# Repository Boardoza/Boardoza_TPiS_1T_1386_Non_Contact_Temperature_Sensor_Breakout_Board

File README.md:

# Boardoza TPiS 1T 1386 L5.5 H Thermopile Sensor Breakout Board

The **Boardoza TPiS 1T 1386 L5.5 H Breakout Board** is a non-contact infrared temperature sensor board designed for makers, developers, and embedded system enthusiasts who need accurate temperature measurements without physical contact. It uses the **Excelitas TPiS 1T 1386 L5.5 H** thermopile sensor to measure object temperature in a fast, hygienic, and contactless way, making it ideal for projects where traditional contact sensors are not suitable.

The onboard sensor provides strong thermal stabilization, ensuring reliable and consistent measurements even under harsh or changing environmental conditions. Communication is handled via the **I²C interface**, allowing easy integration with popular development platforms such as Arduino, ESP32, and Raspberry Pi. This breakout board is well suited for **maker projects and prototypes including non-contact thermometers, industrial temperature monitoring, HVAC systems, smart home applications, medical devices, and general IoT-based temperature sensing solutions**.

## [Click here to purchase!](https://www.ozdisan.com/p/gelistirme-kitleri-ve-aksesuarlari-617/boardoza-tpis-1t-1386-1202719)
| Front Side | Back Side |
|:---:|:---:|
|  |  |

---

## Key Features

- **Non-Contact Temperature Measurement:** Measures object temperature without physical contact using infrared sensing technology.
- **Excelitas Thermopile Sensor:** Equipped with the **TPiS 1T 1386 L5.5 H** medical-grade thermopile sensor.
- **Thermal Stabilization:** Delivers stable and reliable temperature readings even in harsh or changing environmental conditions.
- **I²C Communication Interface:** Standard I²C protocol for easy integration with microcontrollers and development boards.
- **Wide Supply Voltage Support:** Compatible with both **3.3V and 5V** systems.
- **Interrupt Output:** Open-drain, active-low interrupt pin for event-based temperature monitoring.

---

## Technical Specifications

**Model:** TPiS 1T 1386 L5.5 H  
**Manufacturer:** Boardoza  
**Manufacturer IC:** Excelitas Technologies  
**Supply Voltage:** 3.3V - 5V  
**Functions:** Non-contact infrared temperature sensor  
**Communication Interface:** I²C  
**I²C Clock Speed:** Up to 400 kHz (clock stretching supported)  
**Interrupt Output:** Open-drain, active-low  
**Maximum Current per Pin:** −100 mA to +100 mA  
**Storage Temperature:** −40 °C to +105 °C  
**Operating Temperature:** −20 °C to +105 °C  
**Board Dimensions:** 20 mm × 40 mm

---

## Board Pinout

### ( J1 ) I²C & Power Connector

| Pin Number | Pin Name | Description |
|:---:|:---:|---|
| 1 | VCC | Power supply input (3.3V - 5V) |
| 2 | SCL | I²C serial clock line |
| 3 | SDA | I²C bidirectional data line |
| 4 | GND | Ground |

### ( J2 ) Interrupt Connector

| Pin Number | Pin Name | Description |
|:---:|:---:|---|
| 1 | INT | Open-drain, active-low interrupt output. Cleared by reading sensor registers |

---

## Board Dimensions

---

## Step Files

[Boardoza TPiS_1T_1386L5.step](./assets/TPiS_1T_1386L5%20Step.step)

---

## Datasheet

[TPiS 1T 1386 L5.5 H Datasheet.pdf](./assets/TPiS_1T_1386L5%20Datasheet.pdf)

---

## Version History

- V1.0.0 – Initial Release

---

## Support

- If you have any questions or need support, please contact **support@boardoza.com**

---

## **License**

This repository contains both hardware and software components:

### **Hardware Design**

[![CC BY-SA 4.0][cc-by-sa-shield]][cc-by-sa]

All hardware design files are licensed under [Creative Commons Attribution-ShareAlike 4.0 International License][cc-by-sa].

[cc-by-sa]: http://creativecommons.org/licenses/by-sa/4.0/
[cc-by-sa-shield]: https://img.shields.io/badge/License-CC%20BY--SA%204.0-lightgrey.svg

### **Software/Firmware**

[![BSD-3-Clause][bsd-shield]][bsd]

All software and firmware are licensed under [BSD 3-Clause License][bsd].

[bsd]: https://opensource.org/licenses/BSD-3-Clause
[bsd-shield]: https://img.shields.io/badge/License-BSD%203--Clause-blue.svg

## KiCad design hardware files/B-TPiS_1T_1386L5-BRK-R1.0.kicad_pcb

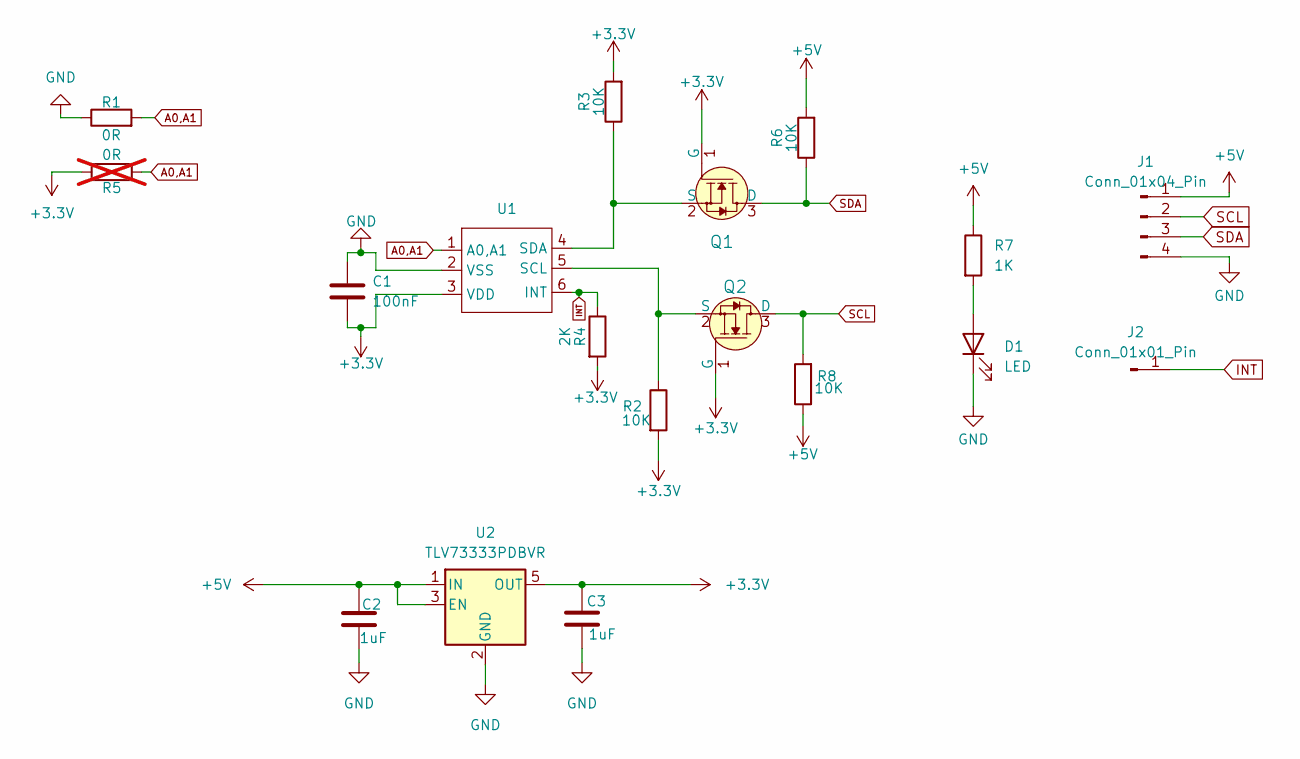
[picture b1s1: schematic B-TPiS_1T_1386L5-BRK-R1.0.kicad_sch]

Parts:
C1: 100nF; C_0603_1608Metric; MPN CL10B104KB8NNNC
C2, C3: 1uF; C_0603_1608Metric; MPN CL10A105KO8NNNC
D1: LED; LED_0603_1608Metric; MPN LTST-C190KRKT
J1: Conn_01x04_Pin; 2317-04S_1x04_P2.50mm_Vertical
J2: Conn_01x01_Pin; PinHeader_1x01_P2.54mm_Vertical
Q1, Q2: 2N7002-7-F; SOT-23-3; MPN 2N7002_R1_00001; Digi-Key_PN 2N7002-FDICT-ND
R1: 0R; R_0603_1608Metric; MPN CRT03J7-R0R0
R2, R3, R6, R8: 10K; R_0603_1608Metric; MPN 0603WGJ0103T5E
R4: 2K; R_0603_1608Metric; MPN 0603SAJ0202T5E
R5: 0R; R_0603_1608Metric; MPN CRT03J7-R0R0; not fitted
R7: 1K; R_0603_1608Metric; MPN CRT03J7E1001
U1: TPiS 1T 1386
U2: TLV73333PDBVR; SOT-23-5

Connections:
+3.3V: C1.2, C3.1, Q1.1 (G), Q2.1 (G), R2.2, R3.2, R4.2, R5.2, U1.3 (VDD), U2.5 (OUT)
+5V: C2.1, J1.1, R6.2, R7.1, R8.1, U2.1 (IN), U2.3 (EN)
A0,A1: R1.2, R5.1, U1.1 (A0,A1)
GND: C1.1, C2.2, C3.2, D1.1 (K), J1.4, R1.1, U1.2 (VSS), U2.2 (GND)
INT: J2.1, R4.1, U1.6 (INT)
unnamed: D1.2 (A), R7.2
unnamed: Q1.2 (S), R3.1, U1.4 (SDA)
unnamed: Q2.2 (S), R2.1, U1.5 (SCL)
SCL: J1.2, Q2.3 (D), R8.2
SDA: J1.3, Q1.3 (D), R6.1

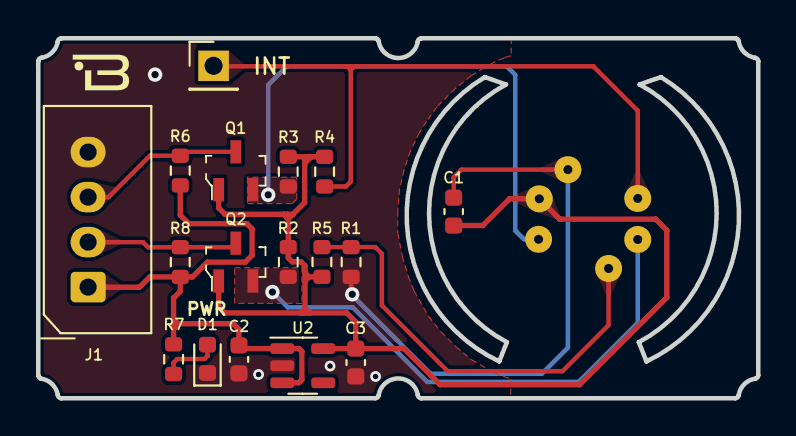
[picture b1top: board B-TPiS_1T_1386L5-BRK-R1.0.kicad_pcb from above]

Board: 2 copper layers, 40.0 x 20.0 mm, 18 parts (1 on the bottom side), 10 nets.
